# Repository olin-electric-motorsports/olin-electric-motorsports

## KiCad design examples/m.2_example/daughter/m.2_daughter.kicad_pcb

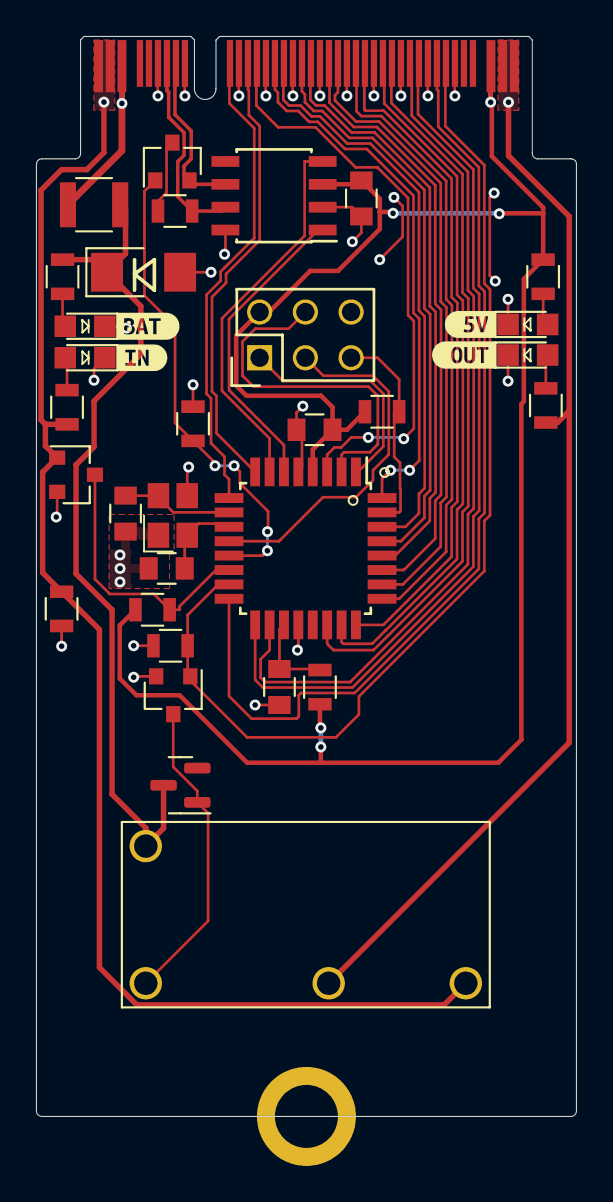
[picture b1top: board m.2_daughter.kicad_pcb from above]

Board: 2 copper layers, 30.0 x 60.0 mm, 37 parts (0 on the bottom side), 42 nets.

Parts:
C1, C2: C_0.1uF; C_0805_OEM
C3: C_100pF; C_0805_OEM
C4, C5: C_30pF; C_0805_OEM
D1, D3, D102, D103: LED_0805; LED_0805_OEM
D2: BAS40-00; SOT-23
D101: D_Zener_18V; DO-214AA
F101: F_500mA_16V; Fuse_1210
H1: MountingHole_Pad; M.2_Mount
J1: CONN_02X03; Pin_Header_Straight_2x03
J2: M.2_BoardEdge; Automotive_M.2_Edge_Connector
K1: G5Q-1A4-DC12; Relay_SPST_OMRON-G5Q-1A4_OEM
Q1, Q2, Q3: SSM3K333R; SOT-23F
R1: R_100; R_0805_OEM
R2: R_120_DNP; R_0805_OEM
R3, R6, R7: R_10K; R_0805_OEM
R4, R11, R101: R_1K; R_0805_OEM
R5: R_100K; R_0805_OEM
R10: R_604K; R_0805_OEM
R105: R_200; R_0805_OEM
U1: MCP2561-E_SN; SOIC-8_3.9x4.9mm_Pitch1.27mm_OEM
U2: ATMEGA16M1; TQFP-32_7x7mm_Pitch0.8mm
Y1: Crystal_SMD; Crystal_SMD_FA238
kibuzzard-634A2231: G***; kibuzzard-634A2231
kibuzzard-6348F6FA: G***; kibuzzard-6348F6FA
kibuzzard-63488F75: G***; kibuzzard-63488F75
kibuzzard-63488FFA: G***; kibuzzard-63488FFA

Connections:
+5V: C1.1, C2.1, J1.2, J2.P38, R1.1, R3.1, R6.1, R105.1, U1.3 (VDD), U2.4 (VCC)
+BATT: F101.2, J2.P3
/BAT_FUSED: D2.3 (K), D101.1 (K), F101.1, K1.5, R101.1
/CAN_+: J2.7, R2.1, U1.7 (CANH)
/CAN_-: J2.8, Q2.2 (S), U1.6 (CANL)
/CAN_RX: U1.4 (RXD), U2.7 ((PCINT11/T1/ICP1B/RXCAN)PC3)
/CAN_TERM_EN: Q2.1 (G), R7.1, U2.13 ((PCINT21/ADC2/ACMP2)PD5)
/CAN_TX: U1.1 (TXD), U2.6 ((PCINT10/T0/TXCAN)PC2)
/MISO: J1.1, U2.1 ((PCINT18/PSCIN2/OC1A/MISO_A)PD2)
/MOSI: J1.4, U2.2 ((PCINT19/TXD/TXLIN/OC0A/~SS/MOSI_A)PD3)
/PB0: J2.12, U2.8 ((PCINT0/MISO/PSCOUT2A)PB0)
/PB1: J2.10, U2.9 ((PCINT1/MOSI/PSCOUT2B)PB1)
/PB2: J2.33, U2.16 ((PCINT2/ADC5/INT1/ACMPN0)PB2)
/PB3: J2.27, U2.23 ((PCINT3/AMP0-)PB3)
/PB4: J2.25, U2.24 ((PCINT4/AMP0+)PB4)
/PB5: J2.22, U2.26 ((PCINT5/ADC6/INT2/ACMPN1/AMP2-)PB5)
/PB6: J2.21, U2.27 ((PCINT6/ADC7/PSCOUT1B)PB6)
/PB7: J2.19, U2.28 ((PCINT7/ADC4/SCK/PSCOUT0B)PB7)
/PC0: J2.16, U2.30 ((PCINT8/INT3/PSCOUT1A)PC0)
/PC1: J2.13, U2.3 ((PCINT9/PSCIN1/OC1B/~SS_A)PC1)
/PC4: J2.31, U2.17 ((PCINT12/ADC8/ACMPN3/AMP1-)PC4)
/PC5: J2.30, U2.18 ((PCINT13/ADC9/ACMP3/AMP1+)PC5)
/PC6: J2.28, U2.22 ((PCINT14/ADC10/ACMP1)PC6)
/PC7: J2.24, U2.25 ((PCINT15/D2A/AMP2+)PC7)
/PD0: J2.18, U2.29 ((PCINT16/PSCOUT0A)PD0)
/PD1: J2.15, U2.32 ((PCINT17/CLKO/PSCIN0)PD1)
/PD7: J2.34, Q3.1 (G), R10.1, U2.15 ((PCINT23/ACMP0)PD7)
/RESET: J1.5, R3.2, U2.31 ((PCINT24/OCD/~RESET)PE0)
/SCK: J1.3, U2.12 ((PCINT20/ADC1/RXD/RXLIN/ICP1A/SCK_A)PD4)
/SHDN_IN: J2.P1, J2.P2, K1.3, Q1.1 (G), R4.1, R5.1
/SHDN_OUT: J2.P39, J2.P40, K1.2, R11.1
/SHDN_SENSE: Q1.3 (D), R6.2, U2.14 ((PCINT22/ADC3/INT0/ACMPN2)PD6)
GND: C1.2, C2.2, C3.2, C4.2, C5.2, D1.1 (K), D3.1 (K), D101.2 (A), D102.1 (K), D103.1 (K), H1.1, J1.6, J2.6, J2.9, J2.11, J2.14, J2.17, J2.20, J2.23, J2.26, J2.29, J2.32, J2.35, Q1.2 (S), Q3.2 (S), R5.2, R7.2, R10.2, U1.2 (VSS), U1.8 (STBY), U2.5 (GND), U2.20 (AGND), Y1.2, Y1.4
unnamed: C3.1, R1.2, U2.19 (AVCC)
unnamed: C4.1, U2.11 ((PCINT26/ADC0/XTAL2)PE2), Y1.1
unnamed: C5.1, U2.10 ((PCINT25/OC0B/XTAL1)PE1), Y1.3
unnamed: D1.2 (A), R4.2
unnamed: D2.1 (A), K1.1, Q3.3 (D)
unnamed: D3.2 (A), R11.2
unnamed: D102.2 (A), R101.2
unnamed: D103.2 (A), R105.2
unnamed: Q2.3 (D), R2.2

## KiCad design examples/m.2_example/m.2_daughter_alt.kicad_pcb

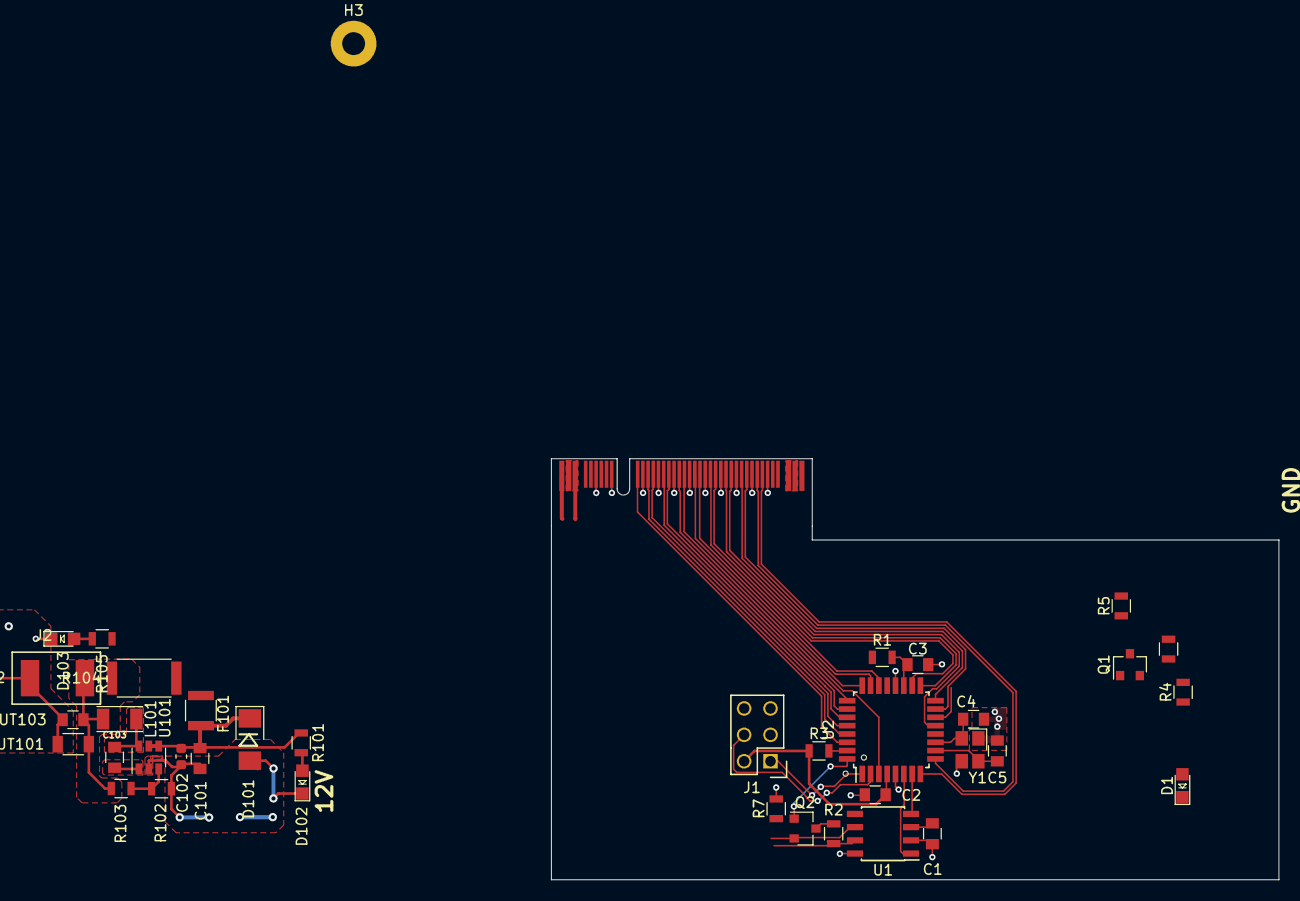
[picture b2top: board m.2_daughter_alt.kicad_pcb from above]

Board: 2 copper layers, 70.0 x 40.5 mm, 38 parts (0 on the bottom side), 44 nets.

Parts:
C1, C2, C101, C103: C_0.1uF; C_0805_OEM
C3: C_100pF; C_0805_OEM
C4, C5: C_30pF; C_0805_OEM
C102: C_2.2uF; C_0603_1608Metric
COUT101: C_22uF; C_1206_OEM
COUT102: C_33uF; Fuse_1812
COUT103: C_47uF; C_0805_OEM
D1, D102, D103: LED_0805; LED_0805_OEM
D101: D_Zener_18V; DO-214AA
F101: F_500mA_16V; Fuse_1210
H3: MountingHole_Pad; MountingHole_2.2mm_M2_Pad
J1: CONN_02X03; Pin_Header_Straight_2x03
J2: M.2_BoardEdge; Automotive_M.2_Edge_Connector
L101: L_100uH; L_100uH_OEM
Q1, Q2: SSM3K333R; SOT-23F
R1: R_100; R_0805_OEM
R2: R_120_DNP; R_0805_OEM
R3, R6, R7: R_10K; R_0805_OEM
R4, R101: R_1K; R_0805_OEM
R5, R103: R_100K; R_0805_OEM
R102: R_25K; R_0805_OEM
R104: R_0_2512; R_2512_OEM
R105: R_200; R_0805_OEM
U1: MCP2561-E_SN; SOIC-8_3.9x4.9mm_Pitch1.27mm_OEM
U2: ATMEGA16M1; TQFP-32_7x7mm_Pitch0.8mm
U101: TPS560430YF; SOT-23-6_OEM
Y1: Crystal_SMD; Crystal_SMD_FA238

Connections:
+5V: C1.1, C2.1, J1.2, R1.1, R3.1, R6.1, R104.1, U1.3 (VDD), U2.4 (VCC)
+BATT: F101.2, J2.P1
/CAN_+: J2.7, R2.1, U1.7 (CANH)
/CAN_-: J2.8, Q2.2 (S), U1.6 (CANL)
/CAN_RX: U1.4 (RXD), U2.7 ((PCINT11/T1/ICP1B/RXCAN)PC3)
/CAN_TERM_EN: Q2.1 (G), R7.1, U2.32 ((PCINT17/CLKO/PSCIN0)PD1)
/CAN_TX: U1.1 (TXD), U2.6 ((PCINT10/T0/TXCAN)PC2)
/MISO: J1.1, U2.1 ((PCINT18/PSCIN2/OC1A/MISO_A)PD2)
/MOSI: J1.4, U2.2 ((PCINT19/TXD/TXLIN/OC0A/~SS/MOSI_A)PD3)
/PB0: J2.34, U2.8 ((PCINT0/MISO/PSCOUT2A)PB0)
/PB1: J2.33, U2.9 ((PCINT1/MOSI/PSCOUT2B)PB1)
/PB2: J2.30, U2.16 ((PCINT2/ADC5/INT1/ACMPN0)PB2)
/PB3: J2.22, U2.23 ((PCINT3/AMP0-)PB3)
/PB4: J2.21, U2.24 ((PCINT4/AMP0+)PB4)
/PB5: J2.16, U2.26 ((PCINT5/ADC6/INT2/ACMPN1/AMP2-)PB5)
/PB6: J2.15, U2.27 ((PCINT6/ADC7/PSCOUT1B)PB6)
/PB7: J2.13, U2.28 ((PCINT7/ADC4/SCK/PSCOUT0B)PB7)
/PC0: J2.10, U2.30 ((PCINT8/INT3/PSCOUT1A)PC0)
/PC1: J2.19, U2.3 ((PCINT9/PSCIN1/OC1B/~SS_A)PC1)
/PC4: J2.27, U2.17 ((PCINT12/ADC8/ACMPN3/AMP1-)PC4)
/PC5: J2.25, U2.18 ((PCINT13/ADC9/ACMP3/AMP1+)PC5)
/PC6: J2.24, U2.22 ((PCINT14/ADC10/ACMP1)PC6)
/PC7: J2.18, U2.25 ((PCINT15/D2A/AMP2+)PC7)
/PD0: J2.12, U2.29 ((PCINT16/PSCOUT0A)PD0)
/PD5: J2.28, U2.13 ((PCINT21/ADC2/ACMP2)PD5)
/PD7: J2.31, U2.15 ((PCINT23/ACMP0)PD7)
/RESET: J1.5, R3.2, U2.31 ((PCINT24/OCD/~RESET)PE0)
/SCK: J1.3, U2.12 ((PCINT20/ADC1/RXD/RXLIN/ICP1A/SCK_A)PD4)
/SHDN_IN: J2.P2, J2.P3, Q1.1 (G), R4.1, R5.1
/SHDN_OUT: J2.P38, J2.P39
/SHDN_SENSE: Q1.3 (D), R6.2, U2.14 ((PCINT22/ADC3/INT0/ACMPN2)PD6)
GND: C1.2, C2.2, C3.2, C4.2, C5.2, C101.2, C102.2, COUT101.2, COUT102.2, COUT103.2, D1.1 (K), D101.2 (A), D102.1 (K), D103.1 (K), H3.1, J1.6, J2.6, J2.9, J2.11, J2.14, J2.17, J2.20, J2.23, J2.26, J2.29, J2.32, J2.35, Q1.2 (S), R5.2, R7.2, R102.2, U1.2 (VSS), U1.8 (STBY), U2.5 (GND), U2.20 (AGND), U101.2 (GND), Y1.2, Y1.4
unnamed: C3.1, R1.2, U2.19 (AVCC)
unnamed: C4.1, U2.11 ((PCINT26/ADC0/XTAL2)PE2), Y1.1
unnamed: C5.1, U2.10 ((PCINT25/OC0B/XTAL1)PE1), Y1.3
unnamed: C101.1, C102.1, D101.1 (K), F101.1, R101.1, U101.4 (EN), U101.5 (VIN)
unnamed: C103.1, U101.1 (CB)
unnamed: C103.2, L101.1, U101.6 (SW)
unnamed: COUT101.1, COUT102.1, COUT103.1, L101.2, R103.1, R104.2, R105.1
unnamed: D1.2 (A), R4.2
unnamed: D102.2 (A), R101.2
unnamed: D103.2 (A), R105.2
unnamed: Q2.3 (D), R2.2
unnamed: R102.1, R103.2, U101.3 (FB)

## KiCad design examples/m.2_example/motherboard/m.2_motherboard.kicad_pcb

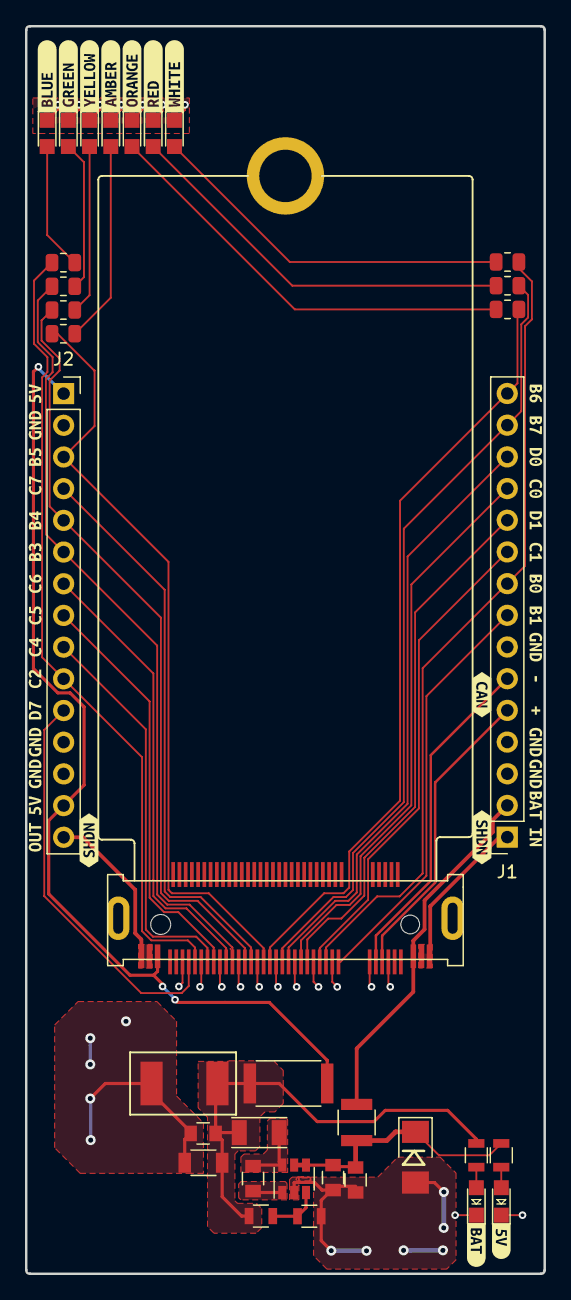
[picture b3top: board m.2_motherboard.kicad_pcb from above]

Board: 2 copper layers, 41.6 x 100.0 mm, 77 parts (0 on the bottom side), 38 nets.

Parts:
C101, C103: C_0.1uF; C_0805_OEM
C102: C_2.2uF; C_0805_OEM
COUT101: C_22uF; C_1206_OEM
COUT102: C_33uF; C_1812
COUT103: C_47uF; C_0805_OEM
D1: LED_BLUE; CHIPLED_0805
D2: LED_GREEN; CHIPLED_0805
D3: LED_YELLOW; CHIPLED_0805
D4: LED_AMBER; CHIPLED_0805
D5: LED_ORANGE; CHIPLED_0805
D6: LED_RED; CHIPLED_0805
D7: LED_WHITE; CHIPLED_0805
D101: D_Zener_18V; DO-214AA
D102, D103: LED_0805; LED_0805_OEM
F101: F_500mA_16V; Fuse_1210
H1: MountingHole_Pad; MountingHole_440_Keystone_4939
J1, J2: Conn_01x15; PinSocket_1x15_P2.54mm_Vertical
J3: M.2; Automotive_M.2
L101: L_100uH; L_100uH_OEM
R1, R2, R3, R4, R5, R6, R7: R; R_0805_2012Metric
R101: R_1K; R_0805_OEM
R102: R_25K; R_0805_OEM
R103: R_100K; R_0805_OEM
R104: R_0_2512; R_2512_OEM
R105: R_200; R_0805_OEM
U101: TPS560430YF; SOT-23-6_OEM
kibuzzard-634A4B3E: G***; kibuzzard-634A4B3E
kibuzzard-634A4B52: G***; kibuzzard-634A4B52
kibuzzard-634A4B76: G***; kibuzzard-634A4B76
kibuzzard-634A4B80: G***; kibuzzard-634A4B80
kibuzzard-634A4B93: G***; kibuzzard-634A4B93
kibuzzard-634A4BA3: G***; kibuzzard-634A4BA3
kibuzzard-634A4BB2: G***; kibuzzard-634A4BB2
kibuzzard-634A5D7A, kibuzzard-634A5D7A#2, kibuzzard-634A5D7A#3: G***; kibuzzard-634A5D7A
kibuzzard-634A5D61, kibuzzard-634A5D61#2: G***; kibuzzard-634A5D61
kibuzzard-634A5DDD: G***; kibuzzard-634A5DDD
kibuzzard-634A5DE2: G***; kibuzzard-634A5DE2
kibuzzard-634A5DF0: G***; kibuzzard-634A5DF0
kibuzzard-634A5E01: G***; kibuzzard-634A5E01
kibuzzard-634A5E1B: G***; kibuzzard-634A5E1B
kibuzzard-634A5E2B: G***; kibuzzard-634A5E2B
kibuzzard-634A5E08: G***; kibuzzard-634A5E08
kibuzzard-634A5E21: G***; kibuzzard-634A5E21
kibuzzard-634A5E38: G***; kibuzzard-634A5E38
kibuzzard-634A5E67: G***; kibuzzard-634A5E67
kibuzzard-634A5E74, kibuzzard-634A5E74#2: G***; kibuzzard-634A5E74
kibuzzard-634A5EAA: G***; kibuzzard-634A5EAA
kibuzzard-634A5EB2: G***; kibuzzard-634A5EB2
kibuzzard-634A5EFD: G***; kibuzzard-634A5EFD
kibuzzard-634A5F2F: G***; kibuzzard-634A5F2F
kibuzzard-634A5F3F: G***; kibuzzard-634A5F3F
kibuzzard-634A5F10: G***; kibuzzard-634A5F10
kibuzzard-634A5F18: G***; kibuzzard-634A5F18
kibuzzard-634A5F21: G***; kibuzzard-634A5F21
kibuzzard-634A5F28: G***; kibuzzard-634A5F28
kibuzzard-634A5F37: G***; kibuzzard-634A5F37
kibuzzard-634A5F48: G***; kibuzzard-634A5F48
kibuzzard-634A5F51: G***; kibuzzard-634A5F51
kibuzzard-634A602F: G***; kibuzzard-634A602F
kibuzzard-634A4103: G***; kibuzzard-634A4103
kibuzzard-634A4119: G***; kibuzzard-634A4119
kibuzzard-634A6037: G***; kibuzzard-634A6037
kibuzzard-634A6045, kibuzzard-634A6045#2: G***; kibuzzard-634A6045

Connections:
+5V: J2.1, J2.14, J3.P38, R104.1
+BATT: F101.2, J1.2, J3.P3
/CAN_+: J1.5, J3.7
/CAN_-: J1.6, J3.8
/PB0: J1.9, J3.12, R7.2
/PB1: J1.8, J3.10
/PB2: J2.10, J3.33, R1.2
/PB3: J2.6, J3.27, R2.2
/PB4: J2.5, J3.25, R3.2
/PB5: J2.3, J3.22, R4.2
/PB6: J1.15, J3.21, R5.2
/PB7: J1.14, J3.19, R6.2
/PC0: J1.12, J3.16
/PC1: J1.10, J3.13
/PC4: J2.9, J3.31
/PC5: J2.8, J3.30
/PC6: J2.7, J3.28
/PC7: J2.4, J3.24
/PD0: J1.13, J3.18
/PD1: J1.11, J3.15
/PD7: J2.11, J3.34
/SHDN_IN: J1.1, J3.P1, J3.P2
/SHDN_OUT: J2.15, J3.P39, J3.P40
GND: C101.2, C102.2, COUT101.2, COUT102.2, COUT103.2, D1.1 (K), D2.1 (K), D3.1 (K), D4.1 (K), D5.1 (K), D6.1 (K), D7.1 (K), D101.2 (A), D102.1 (K), D103.1 (K), H1.1, J1.3, J1.4, J1.7, J2.2, J2.12, J2.13, J3.6, J3.9, J3.11, J3.14, J3.17, J3.20, J3.23, J3.26, J3.29, J3.32, J3.35, R102.2, U101.2 (GND)
unnamed: C101.1, C102.1, D101.1 (K), F101.1, R101.1, U101.4 (EN), U101.5 (VIN)
unnamed: C103.1, U101.1 (CB)
unnamed: C103.2, L101.1, U101.6 (SW)
unnamed: COUT101.1, COUT102.1, COUT103.1, L101.2, R103.1, R104.2, R105.1
unnamed: D1.2 (A), R1.1
unnamed: D2.2 (A), R2.1
unnamed: D3.2 (A), R3.1
unnamed: D4.2 (A), R4.1
unnamed: D5.2 (A), R5.1
unnamed: D6.2 (A), R6.1
unnamed: D7.2 (A), R7.1
unnamed: D102.2 (A), R101.2
unnamed: D103.2 (A), R105.2
unnamed: R102.1, R103.2, U101.3 (FB)
